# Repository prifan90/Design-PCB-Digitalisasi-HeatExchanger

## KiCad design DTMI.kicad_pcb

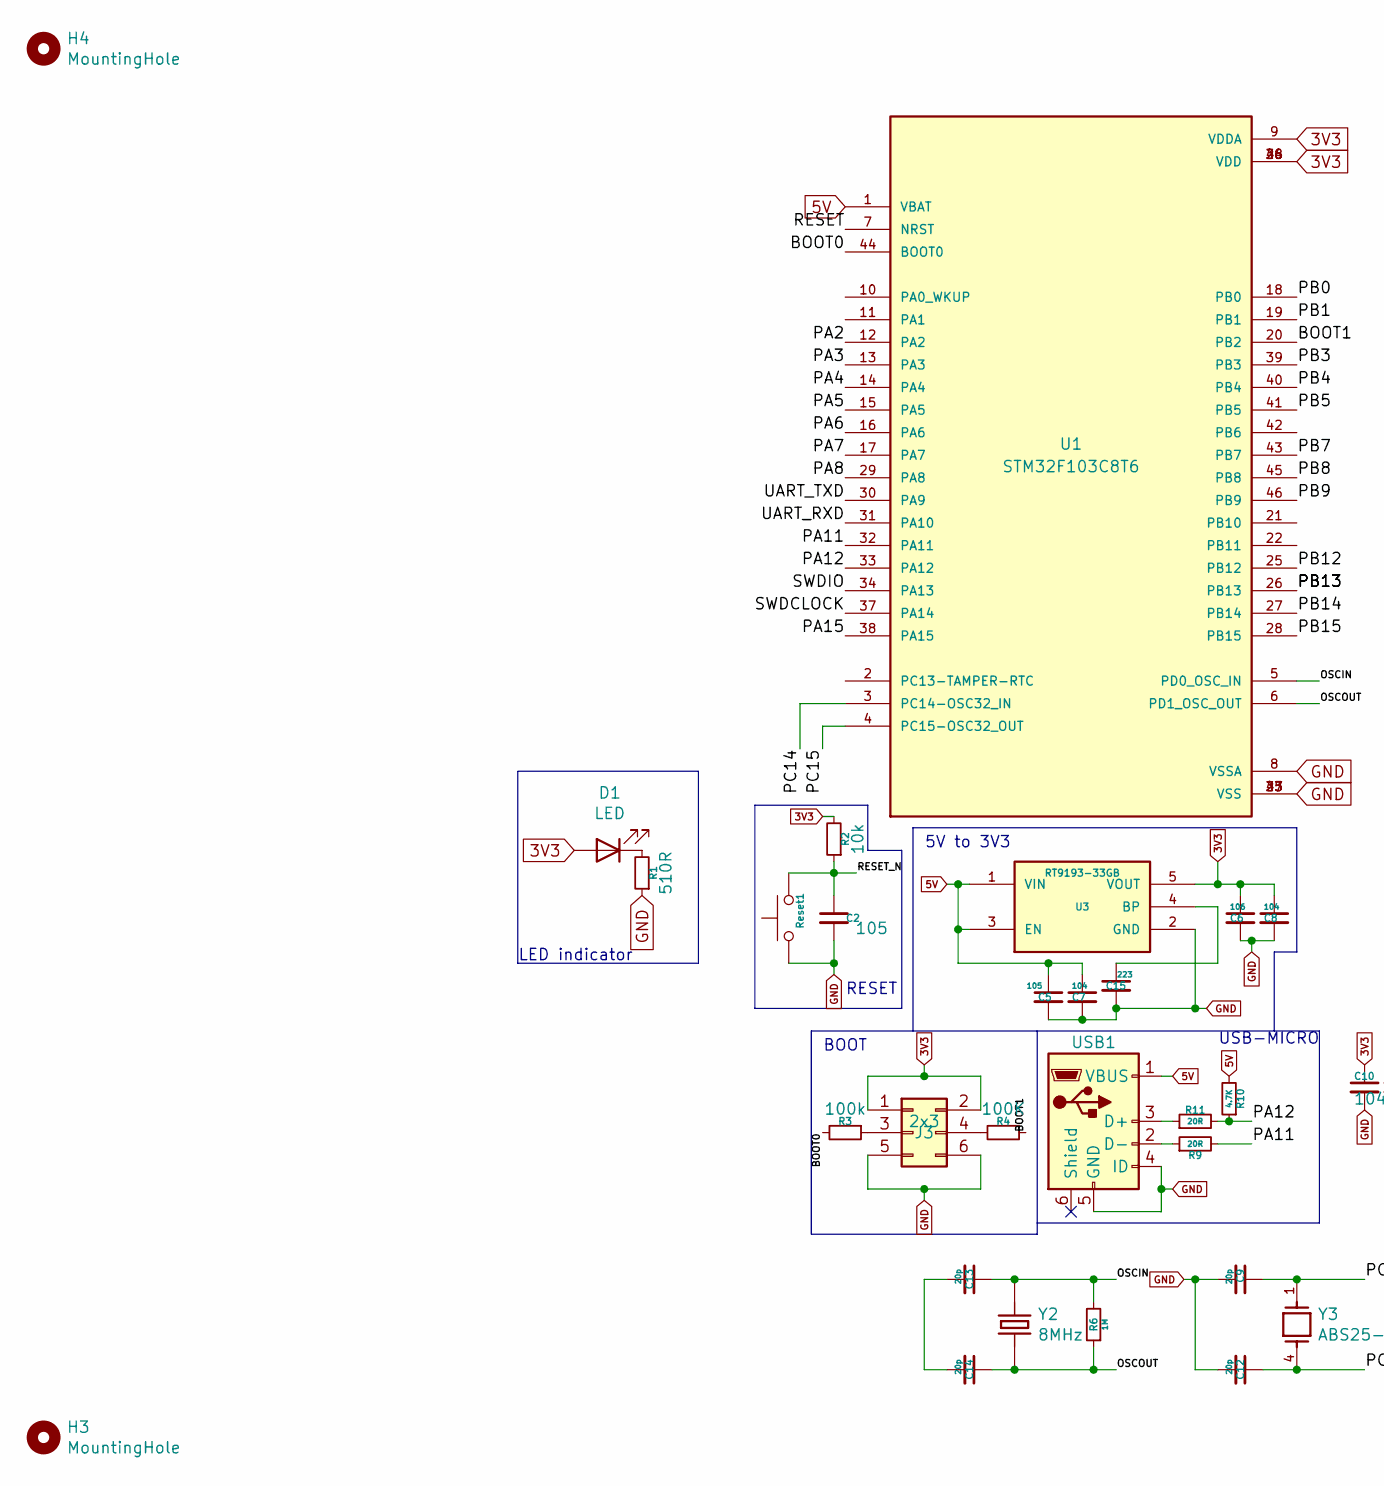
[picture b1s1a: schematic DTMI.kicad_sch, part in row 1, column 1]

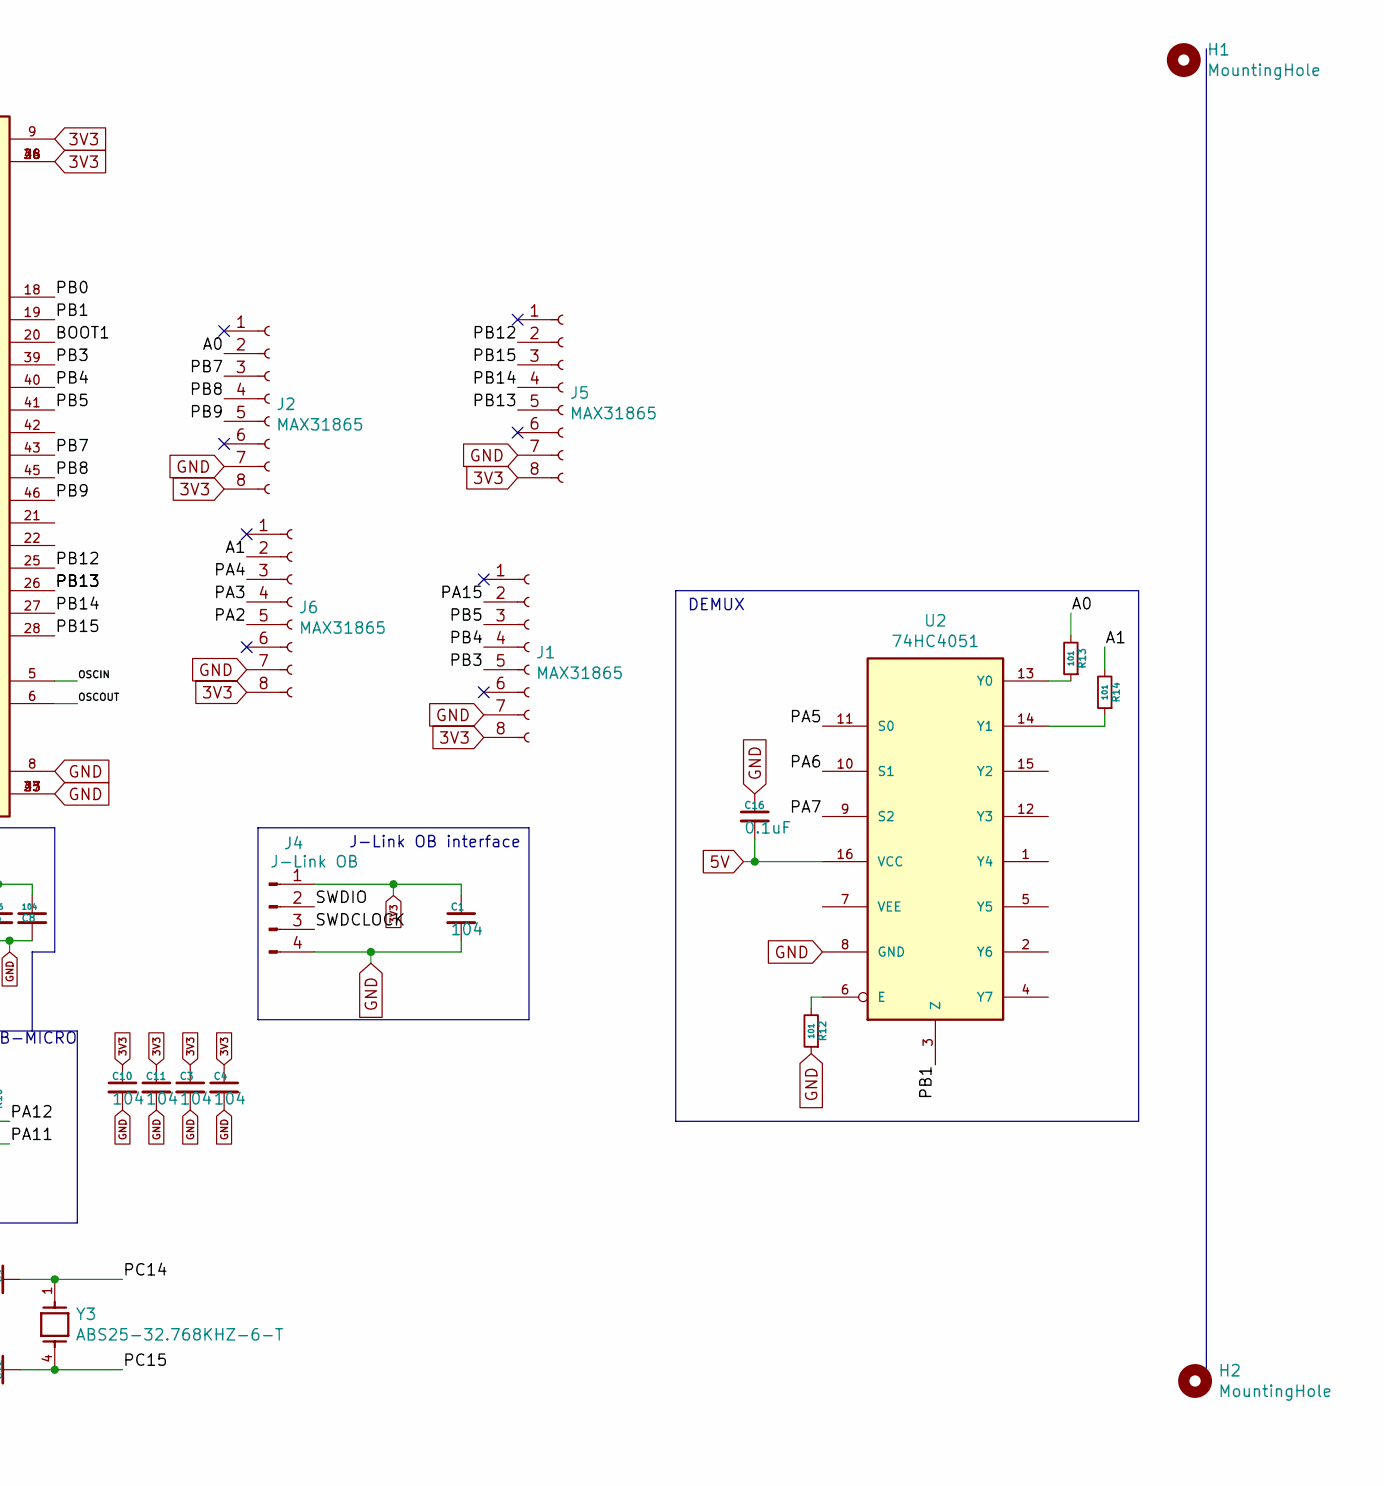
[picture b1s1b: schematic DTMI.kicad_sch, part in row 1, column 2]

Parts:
C1, C3, C4, C7, C8, C10, C11: 104; C_0603_1608Metric_Pad1.08x0.95mm_HandSolder
C2: 105; C_0603_1608Metric_Pad1.08x0.95mm_HandSolder
C5: 105; C_0805_2012Metric_Pad1.18x1.45mm_HandSolder
C6: 106; C_0805_2012Metric_Pad1.18x1.45mm_HandSolder
C9, C12, C13, C14: 20p; C_0603_1608Metric_Pad1.08x0.95mm_HandSolder
C15: 223; C_0603_1608Metric_Pad1.08x0.95mm_HandSolder
C16: 0.1uF; C_0603_1608Metric_Pad1.08x0.95mm_HandSolder
D1: LED; LED_0201_0603Metric_Pad0.64x0.40mm_HandSolder
H1, H2, H3, H4: MountingHole; MountingHole_2.5mm_Pad_Via
J1, J2, J5, J6: MAX31865; PinHeader_1x08_P2.54mm_Vertical
J3: 2x3; PinHeader_2x03_P2.54mm_Vertical
J4: J-Link OB; PinHeader_1x04_P2.54mm_Horizontal
R1: 510R; R_0603_1608Metric_Pad0.98x0.95mm_HandSolder
R2: 10k; R_0603_1608Metric_Pad0.98x0.95mm_HandSolder
R3: 100k; R_0603_1608Metric_Pad0.98x0.95mm_HandSolder
R4: 100K; R_0603_1608Metric_Pad0.98x0.95mm_HandSolder
R6: 1M; R_0603_1608Metric_Pad0.98x0.95mm_HandSolder
R9, R11: 20R; R_0603_1608Metric_Pad0.98x0.95mm_HandSolder
R10: 4.7K; R_0603_1608Metric_Pad0.98x0.95mm_HandSolder
R12, R13, R14: 101; R_1206_3216Metric_Pad1.30x1.75mm_HandSolder
Reset1: SW_Push; SW_SPST_B3U-1000P-B
U1: STM32F103C8T6; QFP50P900X900X160-48N
U2: 74HC4051; SOIC-16_3.9MM
U3: RT9193-33GB; SOT94P279X129-5N
USB1: USB_B_Micro; USB_Micro-B_Wuerth_629105150521
Y2: 8MHz; XTAL_ECS-60-20-4VX
Y3: ABS25-32.768KHZ-6-T; XTAL_ABS25-32.768KHZ-6-T

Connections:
3V3: C1.1, C3.1, C4.1, C6.1, C8.1, C10.1, C11.1, D1.2 (A), J1.8, J2.8, J3.1, J3.2, J4.1, J5.8, J6.8, R2.2, U1.9 (VDDA), U1.24 (VDD), U1.36 (VDD), U1.48 (VDD), U3.5 (VOUT)
5V: C5.1, C7.1, C16.2, R10.2, U1.1 (VBAT), U2.16 (VCC), U3.1 (VIN), U3.3 (EN), USB1.1 (VBUS)
/A0: J2.2, R13.2
/A1: J6.2, R14.2
/BOOT0: R3.2, U1.44 (BOOT0)
/BOOT1: R4.1, U1.20 (PB2)
/OSCIN: C13.1, R6.2, U1.5 (PD0_OSC_IN), Y2.1
/OSCOUT: C14.1, R6.1, U1.6 (PD1_OSC_OUT), Y2.2
/PA2: J6.5, U1.12 (PA2)
/PA3: J6.4, U1.13 (PA3)
/PA4: J6.3, U1.14 (PA4)
/PA5: U1.15 (PA5), U2.11 (S0)
/PA6: U1.16 (PA6), U2.10 (S1)
/PA7: U1.17 (PA7), U2.9 (S2)
/PA11: R9.2, U1.32 (PA11)
/PA12: R10.1, R11.2, U1.33 (PA12)
/PA15: J1.2, U1.38 (PA15)
/PB0: U1.18 (PB0)
/PB1: U1.19 (PB1), U2.3 (Z)
/PB3: J1.5, U1.39 (PB3)
/PB4: J1.4, U1.40 (PB4)
/PB5: J1.3, U1.41 (PB5)
/PB7: J2.3, U1.43 (PB7)
/PB8: J2.4, U1.45 (PB8)
/PB9: J2.5, U1.46 (PB9)
/PB12: J5.2, U1.25 (PB12)
/PB13: J5.5, U1.26 (PB13)
/PB14: J5.4, U1.27 (PB14)
/PB15: J5.3, U1.28 (PB15)
/PC14: C9.1, U1.3 (PC14-OSC32_IN), Y3.1
/PC15: C12.1, U1.4 (PC15-OSC32_OUT), Y3.4
/RESET: U1.7 (NRST)
/RESET_N: C2.1, R2.1, Reset1.2
/SWDCLOCK: J4.3, U1.37 (PA14)
/SWDIO: J4.2, U1.34 (PA13)
/UART_RXD: U1.31 (PA10)
/UART_TXD: U1.30 (PA9)
GND: C1.2, C2.2, C3.2, C4.2, C5.2, C6.2, C7.2, C8.2, C9.2, C10.2, C11.2, C12.2, C15.2, C16.1, J1.7, J2.7, J3.5, J3.6, J4.4, J5.7, J6.7, R1.1, R12.1, Reset1.1, U1.8 (VSSA), U1.23 (VSS), U1.35 (VSS), U1.47 (VSS), U2.8 (GND), U3.2 (GND), USB1.4 (ID), USB1.5 (GND)
unnamed: C13.2, C14.2
unnamed: C15.1, U3.4 (BP)
unnamed: D1.1 (K), R1.2
unnamed: J3.3, R3.1
unnamed: J3.4, R4.2
unnamed: R9.1, USB1.2 (D-)
unnamed: R11.1, USB1.3 (D+)
unnamed: R13.1, U2.13 (Y0)
unnamed: R14.1, U2.14 (Y1)

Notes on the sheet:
USB-MICRO
RESET
DEMUX
J-Link OB interface
LED indicator
5V to 3V3
BOOT

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
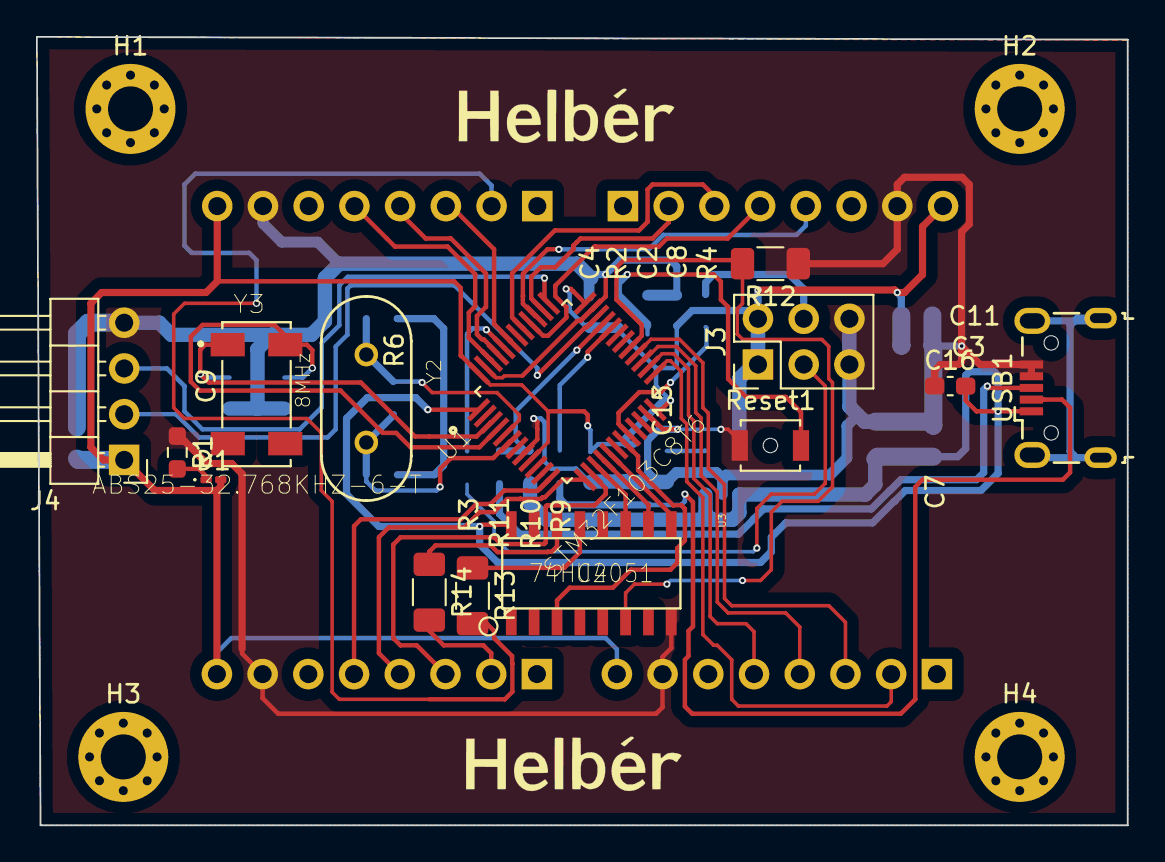
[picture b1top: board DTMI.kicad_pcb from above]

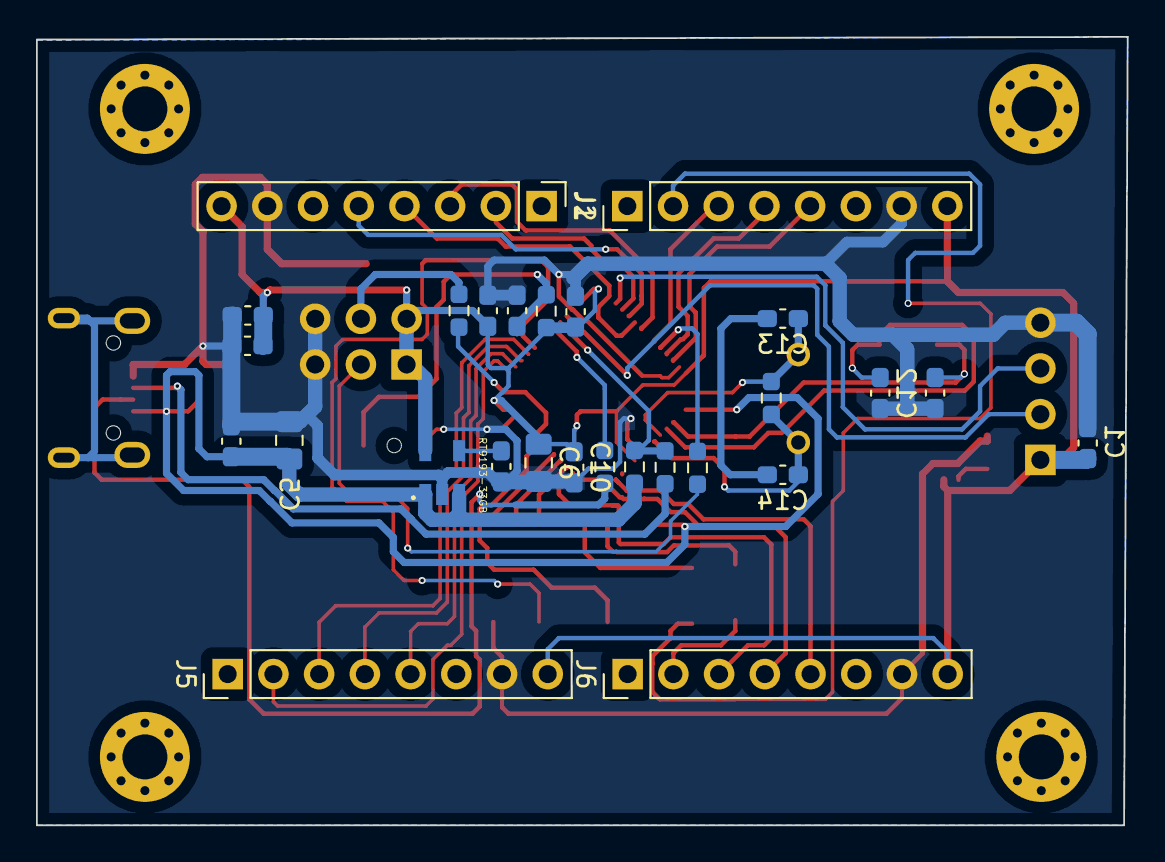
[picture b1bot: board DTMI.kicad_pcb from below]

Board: 2 copper layers, 60.6 x 43.8 mm, 45 parts (27 on the bottom side), 44 nets.

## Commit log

2023-09-20 Design PCB for digitalisasi Heat Exchanger with IC STM32
